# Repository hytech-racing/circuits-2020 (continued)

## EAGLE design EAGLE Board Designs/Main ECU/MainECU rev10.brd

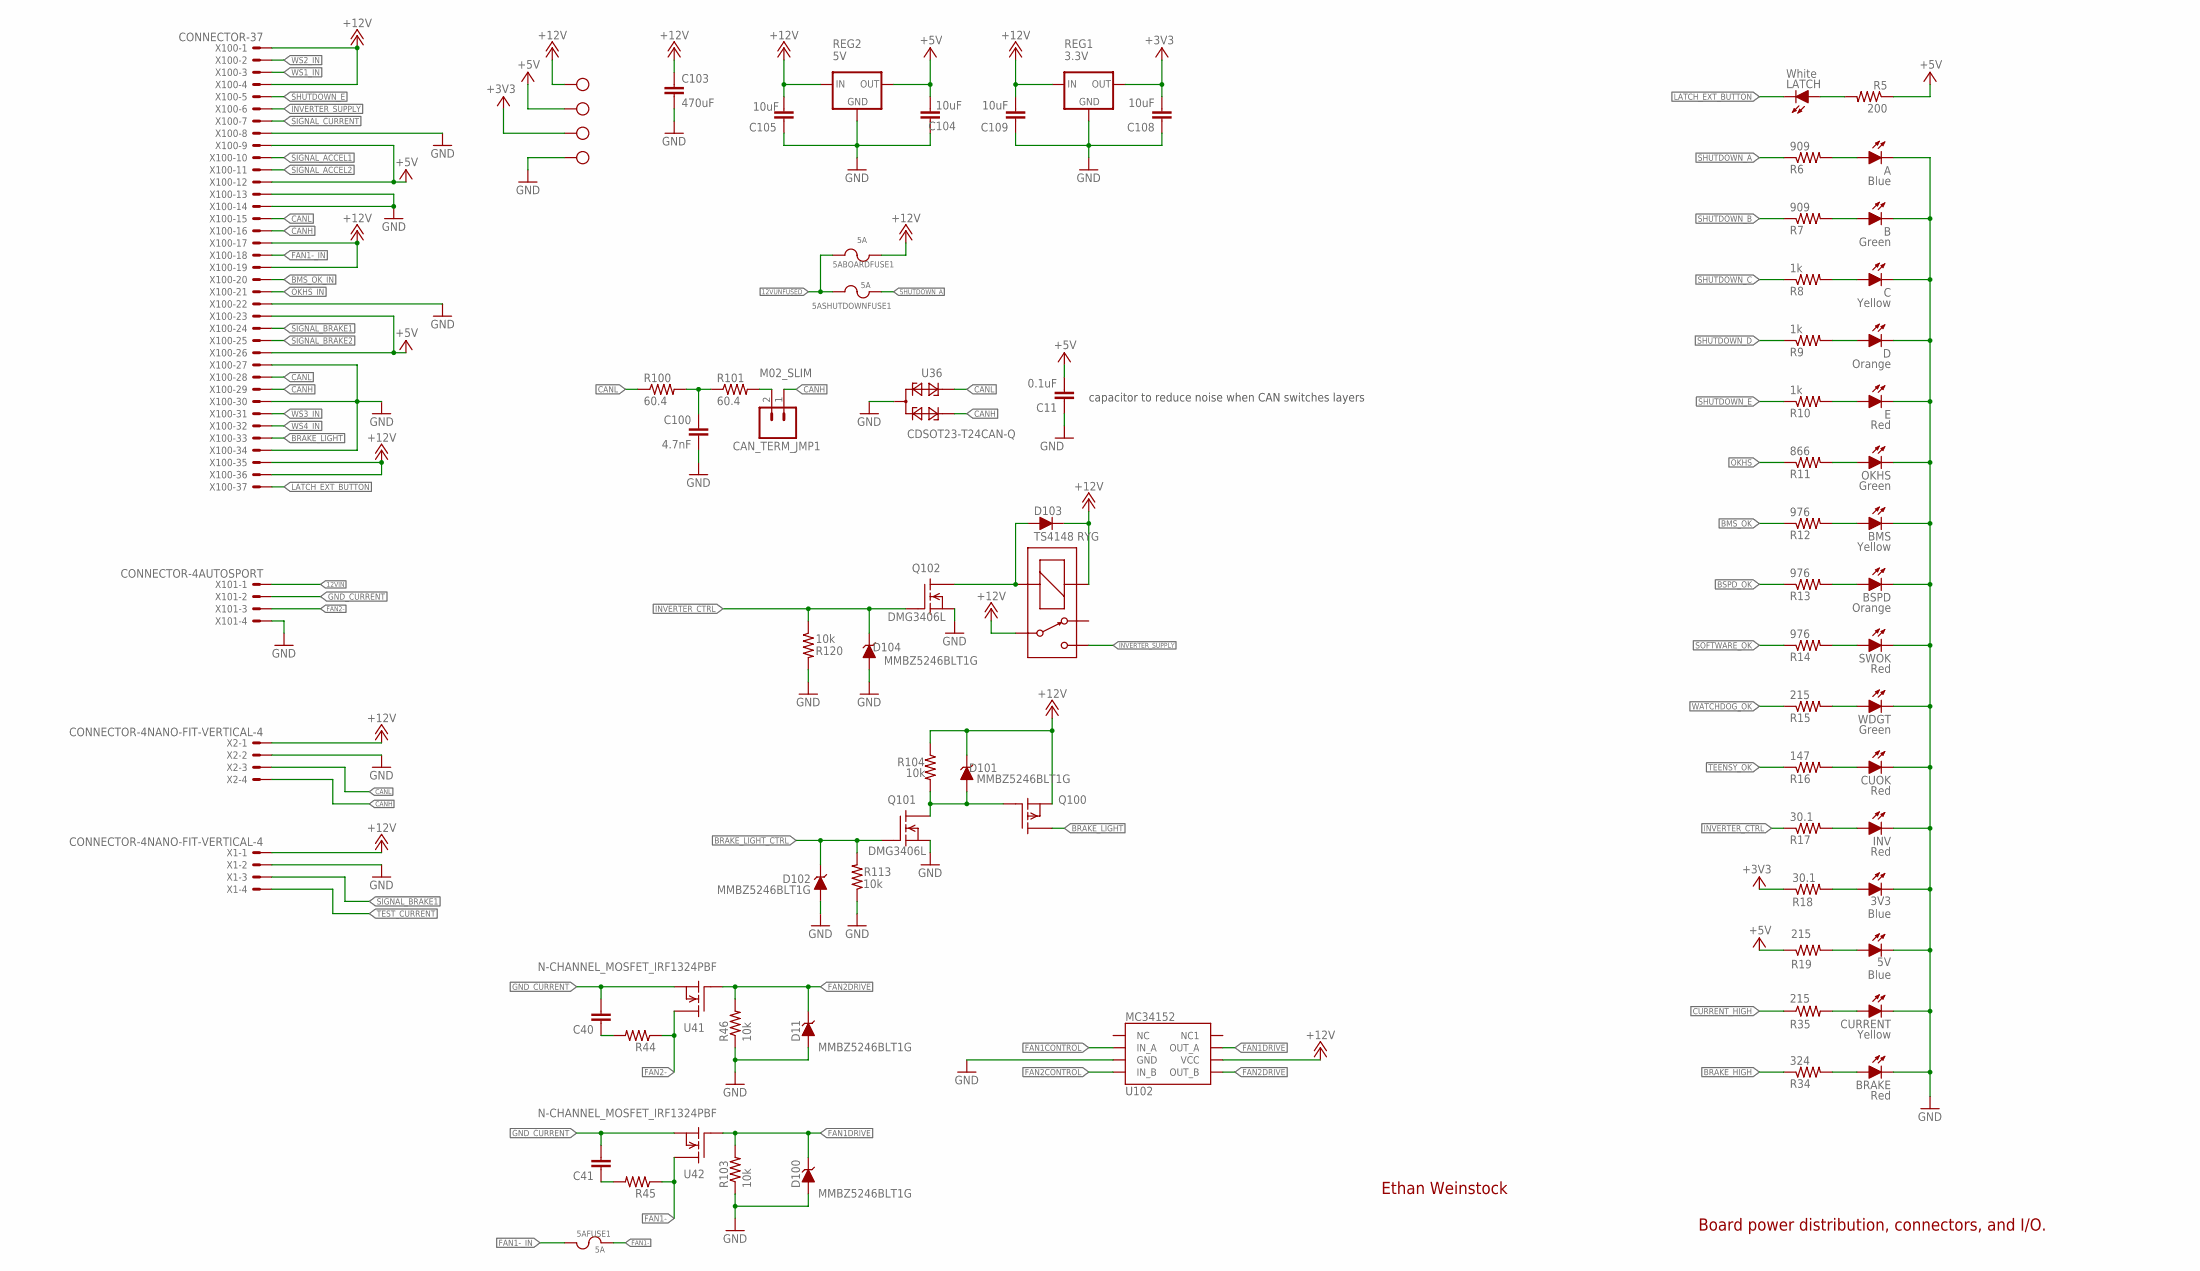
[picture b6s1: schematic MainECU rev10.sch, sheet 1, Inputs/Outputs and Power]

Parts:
3V3, 5V: Blue; LED-805
3V3_TEST: TEST_POINTMICRO_MINIATURE; MICRO_MINIATURE
5ABOARDFUSE1, 5AFUSE1, 5ASHUTDOWNFUSE1: 5A; MINI-BLADE_FUSE_HOLDER
12V_TEST: 12V_TEST; MICRO_MINIATURE
A: Blue; LED-805
B: Green; LED-805
BMS: Yellow; LED-805
BRAKE: Red; LED-805
BSPD: Orange; LED-805
C: Yellow; LED-805
C11: 0.1uF; 0603-CAP
C40, C41: CAP0603-CAP; 0603-CAP
C100: 4.7nF; 0603-CAP
C103: 470uF; CAP-PTH-LARGE
C104, C105, C108, C109: 10uF; 0603-CAP
CAN_TERM_JMP1: M02_SLIM; 1X02_SLIM
CUOK: Red; LED-805
CURRENT: Yellow; LED-805
D: Orange; LED-805
D11, D100, D101, D102, D104: MMBZ5246BLT1G; SOT23
D103: TS4148 RYG; 0805_D
E: Red; LED-805
INV: Red; LED-805
INVERTER_PWR_RELAY1: G5LE; ZF112
LATCH: White; LED-805
OKHS: Green; LED-805
Q100: P-CHANNEL_MOSFET_DMP3099L-7; SOT23
Q101, Q102: DMG3406L; SOT23
R5: 200; 0603-RES
R6, R7: 909; 0603-RES
R8, R9, R10: 1k; 0603-RES
R11: 866; 0603-RES
R12, R13, R14: 976; 0603-RES
R15, R19, R35: 215; 0603-RES
R16: 147; 0603-RES
R17, R18: 30.1; 0603-RES
R34: 324; 0603-RES
R44, R45: RESISTOR0603; 0603-RES
R46, R103, R104, R113, R120: 10k; 0603-RES
R100, R101: 60.4; 0603-RES
REG1: 3.3V; OKI-78SR
REG2: 5V; OKI-78SR
SWOK: Red; LED-805
U36: CDSOT23-T24CAN-Q; SOT23
U40, U43: TEST_POINTMICRO_MINIATURE; MICRO_MINIATURE
U41, U42: N-CHANNEL_MOSFET_IRF1324PBF; TO-220-H-HOLE
U102: MC34152; SOIC-08
WDGT: Green; LED-805
X1, X2: CONNECTOR-4NANO-FIT-VERTICAL-4; NANO-FIT_VERTICAL-4
X100: CONNECTOR-37; AUTOSPORT_14-35
X101: CONNECTOR-4AUTOSPORT; AUTOSPORT_12-04

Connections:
12VIN: X101.P$1; also elsewhere on the board
12VUNFUSED: 5ABOARDFUSE1.L1 (1), 5ABOARDFUSE1.L2 (1), 5ASHUTDOWNFUSE1.L1 (1), 5ASHUTDOWNFUSE1.L2 (1); also elsewhere on the board
+3V3: 3V3_TEST.P$1, C108.2, R18.1, REG1.3 (OUT); also elsewhere on the board
+5V: C11.2, C104.2, R5.1, R19.1, REG2.3 (OUT), U43.P$1, X100.P$9, X100.P$12, X100.P$23, X100.P$26; also elsewhere on the board
+12V: 5ABOARDFUSE1.R1 (2), 5ABOARDFUSE1.R2 (2), 12V_TEST.P$1, C103.1, C105.2, C109.2, D101.3 (C), D103.C, INVERTER_PWR_RELAY1.1 (COIL+), INVERTER_PWR_RELAY1.P, Q100.2 (S), R104.1, REG1.1 (IN), REG2.1 (IN), U102.6 (VCC), X1.P$1, X2.P$1, X100.P$1, X100.P$4, X100.P$17, X100.P$19, X100.P$35, X100.P$36; also elsewhere on the board
BMS_OK: R12.1; also elsewhere on the board
BMS_OK_IN: X100.P$20; also elsewhere on the board
BRAKE_HIGH: R34.1; also elsewhere on the board
BRAKE_LIGHT: Q100.3 (D), X100.P$33
BRAKE_LIGHT_CTRL: D102.3 (C), Q101.1 (G), R113.2; also elsewhere on the board
BSPD_OK: R13.1; also elsewhere on the board
CANH: CAN_TERM_JMP1.1, U36.2, X2.P$4, X100.P$16, X100.P$29; also elsewhere on the board
CANL: R100.1, U36.1, X2.P$3, X100.P$15, X100.P$28; also elsewhere on the board
CURRENT_HIGH: R35.1; also elsewhere on the board
FAN1-: 5AFUSE1.R1 (2), 5AFUSE1.R2 (2), R45.1, U42.2 (D)
FAN1-_IN: 5AFUSE1.L1 (1), 5AFUSE1.L2 (1), X100.P$18
FAN1CONTROL: U102.2 (IN_A); also elsewhere on the board
FAN1DRIVE: D100.3 (C), R103.2, U42.1 (G), U102.7 (OUT_A)
FAN2-: R44.1, U41.2 (D), X101.P$3
FAN2CONTROL: U102.4 (IN_B); also elsewhere on the board
FAN2DRIVE: D11.3 (C), R46.2, U41.1 (G), U102.5 (OUT_B)
GND: 3V3.C, 5V.C, A.C, B.C, BMS.C, BRAKE.C, BSPD.C, C.C, C11.1, C100.2, C103.2, C104.1, C105.1, C108.1, C109.1, CUOK.C, CURRENT.C, D.C, D11.1 (A), D100.1 (A), D102.1 (A), D104.1 (A), E.C, INV.C, OKHS.C, Q101.2 (S), Q102.2 (S), R46.1, R103.1, R113.1, R120.2, REG1.2 (GND), REG2.2 (GND), SWOK.C, U36.3, U40.P$1, U102.3 (GND), WDGT.C, X1.P$2, X2.P$2, X100.P$8, X100.P$13, X100.P$14, X100.P$22, X100.P$27, X100.P$30, X100.P$34, X101.P$4; also elsewhere on the board
GND_CURRENT: C40.2, C41.2, U41.3 (S), U42.3 (S), X101.P$2; also elsewhere on the board
INVERTER_CTRL: D104.3 (C), Q102.1 (G), R17.1, R120.1; also elsewhere on the board
INVERTER_SUPPLY: INVERTER_PWR_RELAY1.S, X100.P$6
LATCH_EXT_BUTTON: LATCH.C, X100.P$37; also elsewhere on the board
unnamed: E.A, R10.2
unnamed: R14.2, SWOK.A
unnamed: R15.2, WDGT.A
unnamed: CUOK.A, R16.2
unnamed: A.A, R6.2
unnamed: 3V3.A, R18.2
unnamed: C40.1, R44.2
unnamed: C41.1, R45.2
unnamed: B.A, R7.2
unnamed: C.A, R8.2
unnamed: LATCH.A, R5.2
unnamed: OKHS.A, R11.2
unnamed: BMS.A, R12.2
unnamed: CURRENT.A, R35.2
unnamed: BRAKE.A, R34.2
unnamed: BSPD.A, R13.2
unnamed: 5V.A, R19.2
unnamed: D101.1 (A), Q100.1 (G), Q101.3 (D), R104.2
unnamed: D.A, R9.2
unnamed: INV.A, R17.2
unnamed: D103.A, INVERTER_PWR_RELAY1.2 (COIL-), Q102.3 (D)
unnamed: CAN_TERM_JMP1.2, R101.2
unnamed: C100.1, R100.2, R101.1
OKHS: R11.1; also elsewhere on the board
OKHS_IN: X100.P$21; also elsewhere on the board
SHUTDOWN_A: 5ASHUTDOWNFUSE1.R1 (2), 5ASHUTDOWNFUSE1.R2 (2), R6.1; also elsewhere on the board
SHUTDOWN_B: R7.1; also elsewhere on the board
SHUTDOWN_C: R8.1; also elsewhere on the board
SHUTDOWN_D: R9.1; also elsewhere on the board
SHUTDOWN_E: R10.1, X100.P$5; also elsewhere on the board
SIGNAL_ACCEL1: X100.P$10; also elsewhere on the board
SIGNAL_ACCEL2: X100.P$11; also elsewhere on the board
SIGNAL_BRAKE1: X1.P$3, X100.P$24; also elsewhere on the board
SIGNAL_BRAKE2: X100.P$25; also elsewhere on the board
SIGNAL_CURRENT: X100.P$7; also elsewhere on the board
SOFTWARE_OK: R14.1; also elsewhere on the board
TEENSY_OK: R16.1; also elsewhere on the board
TEST_CURRENT: X1.P$4; also elsewhere on the board
WATCHDOG_OK: R15.1; also elsewhere on the board
WS1_IN: X100.P$3; also elsewhere on the board
WS2_IN: X100.P$2; also elsewhere on the board
WS3_IN: X100.P$31; also elsewhere on the board
WS4_IN: X100.P$32; also elsewhere on the board

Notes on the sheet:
Ethan Weinstock
Board power distribution, connectors, and I/O.
capacitor to reduce noise when CAN switches layers

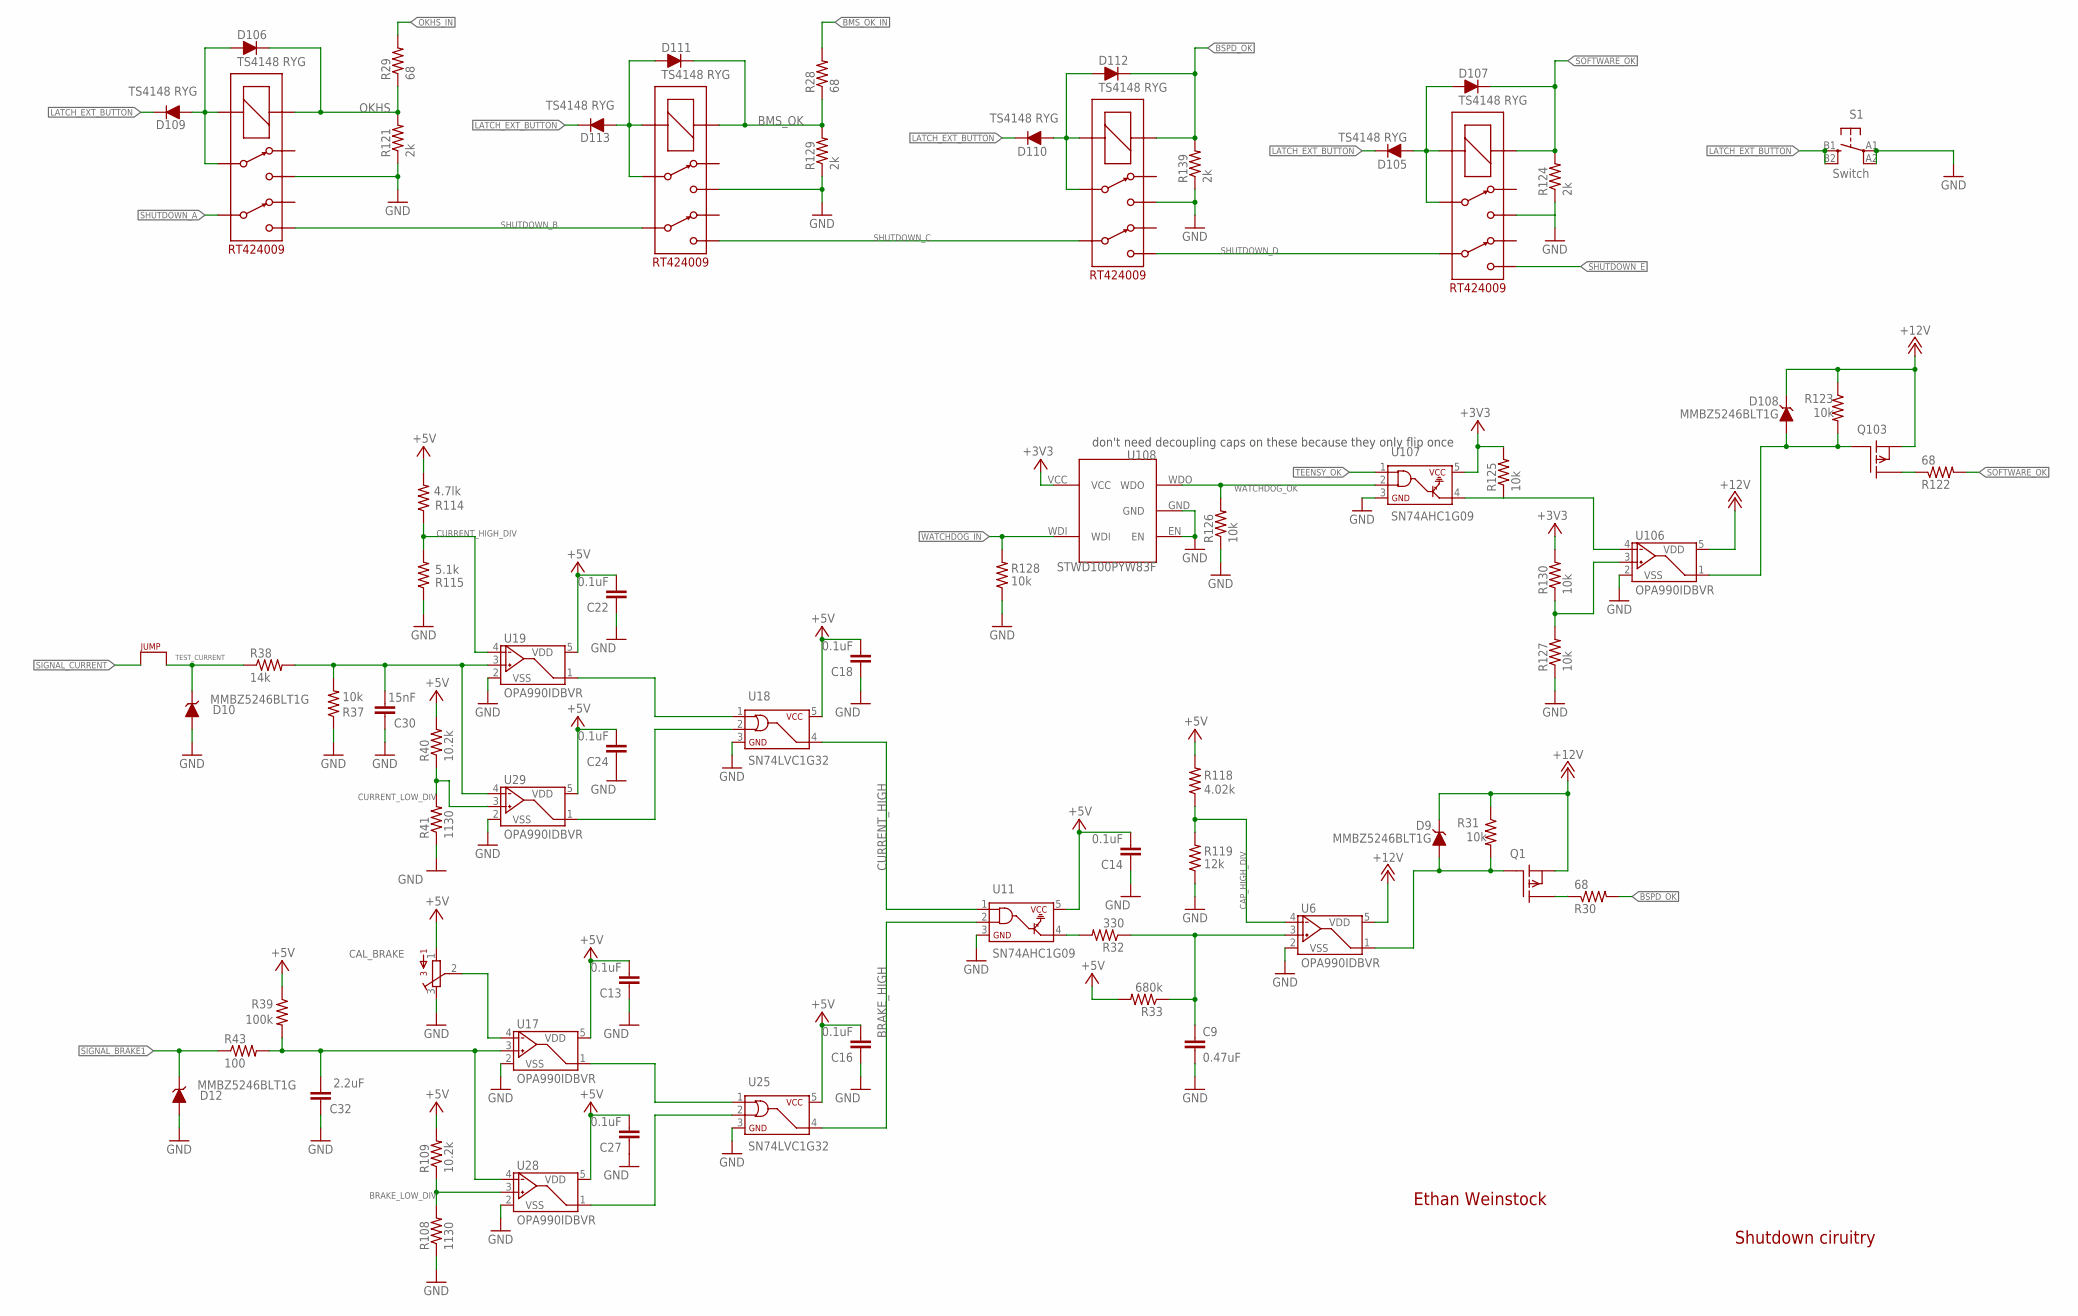
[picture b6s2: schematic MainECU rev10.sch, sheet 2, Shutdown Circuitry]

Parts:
C9: 0.47uF; 0603-CAP
C13, C14, C16, C18, C22, C24, C27: 0.1uF; 0603-CAP
C30: 15nF; 0603-CAP
C32: 2.2uF; 0603-CAP
CAL_BRAKE: TRIMPOT_3296C; TRIMPOT_3296
D9, D10, D12, D108: MMBZ5246BLT1G; SOT23
D105, D106, D107, D109, D110, D111, D112, D113: TS4148 RYG; 0805_D
IMD_SHUTDOWN_RLY1: RT424009; RELAY_DPDT
J1: JUMPER.1; 1X02
Q1, Q103: P-CHANNEL_MOSFET_DMP3099L-7; SOT23
R28, R29, R30, R122: 68; 0603-RES
R31, R37, R123, R125, R126, R127, R128, R130: 10k; 0603-RES
R32: 330; 0603-RES
R33: 680k; 0603-RES
R38: 14k; 0603-RES
R39: 100k; 0603-RES
R40, R109: 10.2k; 0603-RES
R41, R108: 1130; 0603-RES
R43: 100; 0603-RES
R114: 4.7lk; 0603-RES
R115: 5.1k; 0603-RES
R118: 4.02k; 0603-RES
R119: 12k; 0603-RES
R121, R124, R129, R139: 2k; 0603-RES
S1: Switch; TACTILE_SWITCH_SMD_6.2MM_TALL
U2, U3, U4: RT424009; RELAY_DPDT
U6, U17, U19, U28, U29, U106: OPA990IDBVR; SOT-23-5
U11, U107: SN74AHC1G09; SOT-23-5
U18, U25: SN74LVC1G32; SOT-23-5
U108: STWD100PYW83F; SOT323-5

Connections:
+3V3: R125.2, R130.2, U107.5, U108.VCC; also elsewhere on the board
+5V: C13.2, C14.2, C16.2, C18.2, C22.2, C24.2, C27.2, CAL_BRAKE.1, R33.2, R39.1, R40.2, R109.2, R114.2, R118.2, U11.5, U17.5 (VDD), U18.5 (VCC), U19.5 (VDD), U25.5 (VCC), U28.5 (VDD), U29.5 (VDD); also elsewhere on the board
+12V: D9.3 (C), D108.3 (C), Q1.2 (S), Q103.2 (S), R31.1, R123.1, U6.5 (VDD), U106.5 (VDD); also elsewhere on the board
BMS_OK: D111.C, R28.1, R129.2, U3.COIL+; also elsewhere on the board
BMS_OK_IN: R28.2; also elsewhere on the board
BMS_PWR_STEP1: D111.A, D113.A, U3.3, U3.COIL-
BRAKE_HIGH: U11.2, U25.4 (Y); also elsewhere on the board
BRAKE_LOW_DIV: R108.2, R109.1, U28.3 (VIN+)
BSPD_OK: D112.C, R30.2, R139.2, U2.COIL+; also elsewhere on the board
CAP_HIGH_DIV: R118.1, R119.2, U6.4 (VIN-)
CURRENT_HIGH: U11.1, U18.4 (Y); also elsewhere on the board
CURRENT_HIGH_DIV: R114.1, R115.2, U19.4 (VIN-)
CURRENT_LOW_DIV: R40.1, R41.2, U29.3 (VIN+)
GND: C9.2, C13.1, C14.1, C16.1, C18.1, C22.1, C24.1, C27.1, C30.1, C32.1, CAL_BRAKE.3, D10.1 (A), D12.1 (A), IMD_SHUTDOWN_RLY1.4, R37.1, R41.1, R108.1, R115.1, R119.1, R121.1, R124.1, R126.1, R127.1, R128.1, R129.1, R139.1, S1.A1, S1.A2 (P1), U2.4, U3.4, U4.4, U6.2 (VSS), U11.3, U17.2 (VSS), U18.3 (GND), U19.2 (VSS), U25.3 (GND), U28.2 (VSS), U29.2 (VSS), U106.2 (VSS), U107.3, U108.EN, U108.GND; also elsewhere on the board
IMD_PWR_STEP1: D106.A, D109.A, IMD_SHUTDOWN_RLY1.3, IMD_SHUTDOWN_RLY1.COIL-
LATCH_EXT_BUTTON: D105.C, D109.C, D110.C, D113.C, S1.B1 (S), S1.B2 (S1); also elsewhere on the board
unnamed: Q1.3 (D), R30.1
unnamed: C32.2, R39.2, R43.2, U17.3 (VIN+), U28.4 (VIN-)
unnamed: U17.1 (VOUT), U25.1 (A)
unnamed: D105.A, D107.A, U4.3, U4.COIL-
unnamed: U25.2 (B), U28.1 (VOUT)
unnamed: D108.1 (A), Q103.1 (G), R123.2, U106.1 (VOUT)
unnamed: Q103.3 (D), R122.1
unnamed: CAL_BRAKE.2, U17.4 (VIN-)
unnamed: U18.1 (A), U19.1 (VOUT)
unnamed: U18.2 (B), U29.1 (VOUT)
unnamed: R125.1, U106.4 (VIN-), U107.4
unnamed: R127.2, R130.1, U106.3 (VIN+)
unnamed: D110.A, D112.A, U2.3, U2.COIL-
unnamed: C30.2, R37.2, R38.2, U19.3 (VIN+), U29.4 (VIN-)
unnamed: R32.2, U11.4
unnamed: C9.1, R32.1, R33.1, U6.3 (VIN+)
unnamed: D9.1 (A), Q1.1 (G), R31.2, U6.1 (VOUT)
OKHS: D106.C, IMD_SHUTDOWN_RLY1.COIL+, R29.1, R121.2; also elsewhere on the board
OKHS_IN: R29.2; also elsewhere on the board
SHUTDOWN_A: IMD_SHUTDOWN_RLY1.6; also elsewhere on the board
SHUTDOWN_B: IMD_SHUTDOWN_RLY1.5, U3.6; also elsewhere on the board
SHUTDOWN_C: U2.6, U3.5; also elsewhere on the board
SHUTDOWN_D: U2.5, U4.6; also elsewhere on the board
SHUTDOWN_E: U4.5; also elsewhere on the board
SIGNAL_BRAKE1: D12.3 (C), R43.1; also elsewhere on the board
SIGNAL_CURRENT: J1.1; also elsewhere on the board
SOFTWARE_OK: D107.C, R122.2, R124.2, U4.COIL+; also elsewhere on the board
TEENSY_OK: U107.1; also elsewhere on the board
TEST_CURRENT: D10.3 (C), J1.2, R38.1; also elsewhere on the board
WATCHDOG_IN: R128.2, U108.WDI; also elsewhere on the board
WATCHDOG_OK: R126.2, U107.2, U108.WDO; also elsewhere on the board

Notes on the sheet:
Ethan Weinstock
Shutdown ciruitry
don't need decoupling caps on these because they only flip once

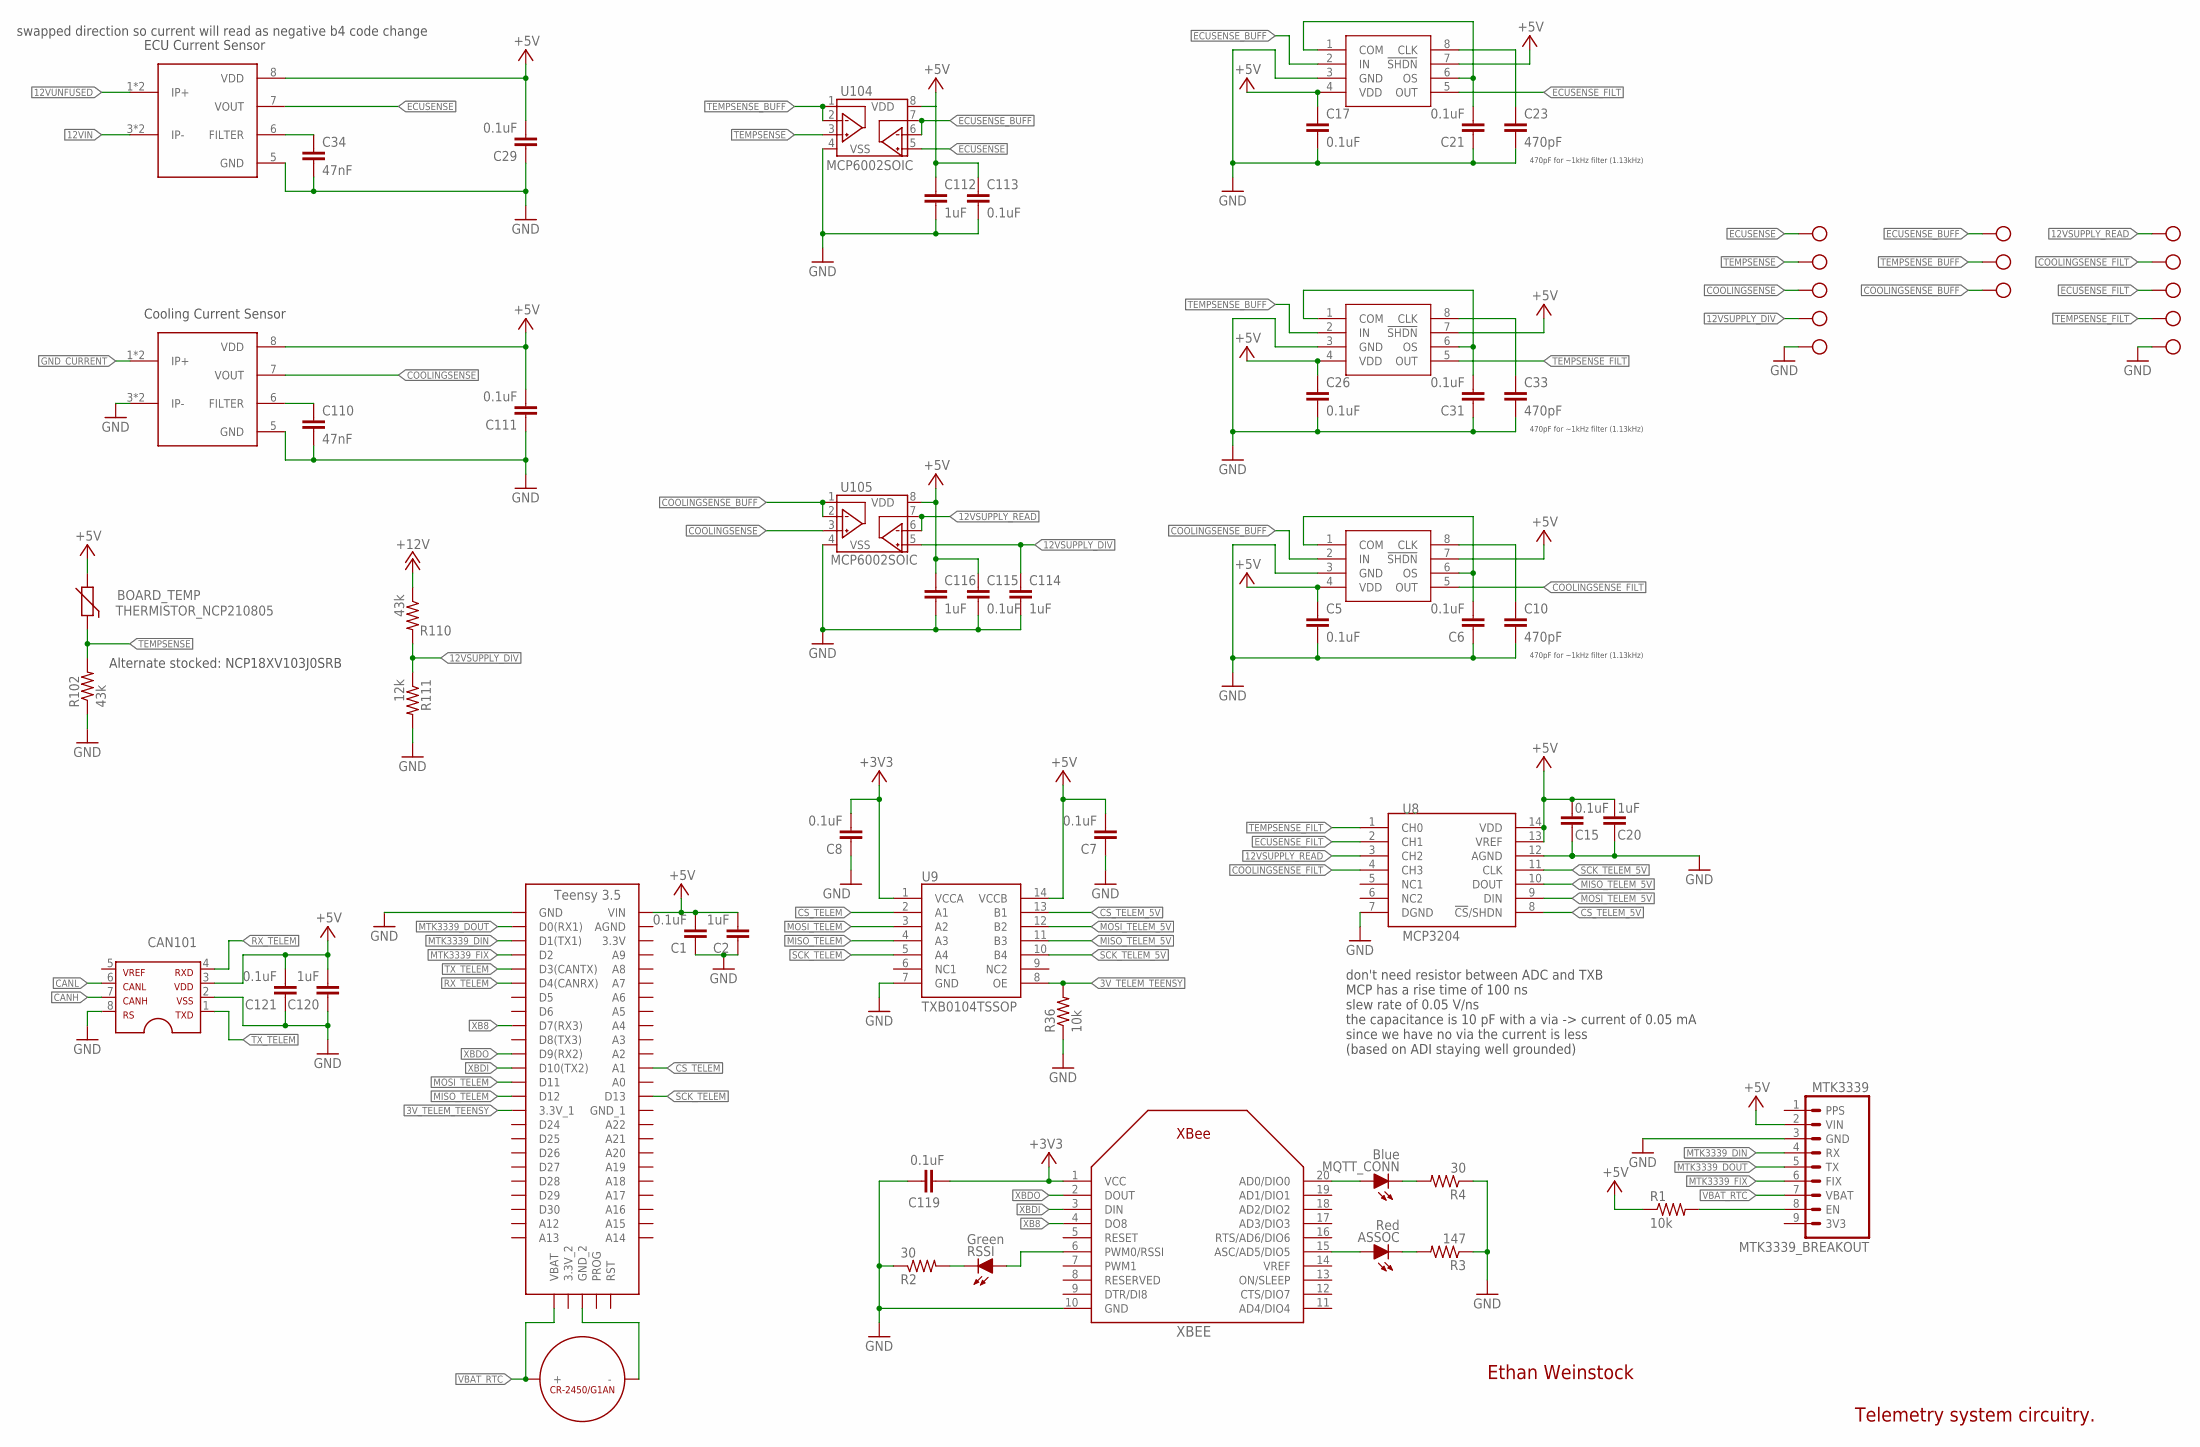
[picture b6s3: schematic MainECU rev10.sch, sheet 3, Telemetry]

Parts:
ASSOC: Red; LED-805
BOARD_TEMP: THERMISTOR_NCP210805; 0805
C1, C5, C6, C7, C8, C15, C17, C21, C26, C29, C31, C111, C113, C115, C119, C121: 0.1uF; 0603-CAP
C2, C20, C112, C114, C116, C120: 1uF; 0603-CAP
C10, C23, C33: 470pF; 0603-CAP
C34, C110: 47nF; 0603-CAP
CAN101: MCP2551; SOIC-08
MQTT_CONN: Blue; LED-805
MTK3339_BREAKOUT: MTK3339; 1X09
R1, R36: 10k; 0603-RES
R2, R4: 30; 0603-RES
R3: 147; 0603-RES
R102, R110: 43k; 0603-RES
R111: 12k; 0603-RES
RSSI: Green; LED-805
U1: TEENSY_3.5_EXT
U7, U24, U33: MAX7480; SOIC-08
U8: MCP3204; SO14
U9: TXB0104TSSOP; TSSOP-14
U12, U13, U14, U15, U16, U20, U21, U22, U26, U27, U30, U31, U32: TEST_POINTMICRO_MINIATURE; MICRO_MINIATURE
U35, U103: ACHS-7121; SOP8
U104, U105: MCP6002SOIC; SOIC-08
U109: CR-2450/G1AN
XBEE: XBEE

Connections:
3V_TELEM_TEENSY: R36.2, U1.3.3V_1, U9.8 (OE)
12VIN: U35.3 (IP-), U35.4 (IP-); also elsewhere on the board
12VSUPPLY_DIV: C114.1, R110.2, R111.1, U16.P$1, U105.5 (VINB+)
12VSUPPLY_READ: U8.3 (CH2), U15.P$1, U105.6 (VINB-), U105.7 (VOUTB)
12VUNFUSED: U35.1 (IP+), U35.2 (IP+); also elsewhere on the board
+3V3: C8.2, C119.1, U9.1 (VCCA), XBEE.1 (VCC); also elsewhere on the board
+5V: BOARD_TEMP.1, C1.2, C2.2, C5.1, C7.2, C15.2, C17.1, C20.2, C26.1, C29.2, C111.2, C112.1, C113.1, C115.1, C116.1, C120.2, C121.2, CAN101.3, MTK3339_BREAKOUT.2 (VIN), R1.1, U1.VIN, U7.4 (VDD), U7.7 (!SHDN), U8.13 (VREF), U8.14 (VDD), U9.14 (VCCB), U24.4 (VDD), U24.7 (!SHDN), U33.4 (VDD), U33.7 (!SHDN), U35.8 (VDD), U103.8 (VDD), U104.8 (VDD), U105.8 (VDD); also elsewhere on the board
+12V: R110.1; also elsewhere on the board
CANH: CAN101.7; also elsewhere on the board
CANL: CAN101.6; also elsewhere on the board
COOLINGSENSE: U21.P$1, U103.7 (VOUT), U105.3 (VINA+)
COOLINGSENSE_BUFF: U7.2 (IN), U12.P$1, U105.1 (VOUTA), U105.2 (VINA-)
COOLINGSENSE_FILT: U7.5 (OUT), U8.4 (CH3), U20.P$1
CS_TELEM: U1.A1, U9.2 (A1)
CS_TELEM_5V: U8.8 (!CS!/SHDN), U9.13 (B1)
ECUSENSE: U27.P$1, U35.7 (VOUT), U104.5 (VINB+)
ECUSENSE_BUFF: U13.P$1, U24.2 (IN), U104.6 (VINB-), U104.7 (VOUTB)
ECUSENSE_FILT: U8.2 (CH1), U24.5 (OUT), U26.P$1
GND: C1.1, C2.1, C5.2, C6.1, C7.1, C8.1, C10.2, C15.1, C17.2, C20.1, C21.1, C23.2, C26.2, C29.1, C31.1, C33.2, C34.2, C110.2, C111.1, C112.2, C113.2, C114.2, C115.2, C116.2, C119.2, C120.1, C121.1, CAN101.2, CAN101.8, MTK3339_BREAKOUT.3 (GND), R2.1, R3.1, R4.1, R36.1, R102.1, R111.2, U1.GND, U7.3 (GND), U8.7 (DGND), U8.12 (AGND), U9.7 (GND), U22.P$1, U24.3 (GND), U32.P$1, U33.3 (GND), U35.5 (GND), U103.3 (IP-), U103.4 (IP-), U103.5 (GND), U104.4 (VSS), U105.4 (VSS), XBEE.10 (GND); also elsewhere on the board
GND_CURRENT: U103.1 (IP+), U103.2 (IP+); also elsewhere on the board
MISO_TELEM: U1.D12, U9.4 (A3)
MISO_TELEM_5V: U8.10 (DOUT), U9.11 (B3)
MOSI_TELEM: U1.D11, U9.3 (A2)
MOSI_TELEM_5V: U8.9 (DIN), U9.12 (B2)
MTK3339_DIN: MTK3339_BREAKOUT.4 (RX), U1.D1(TX1)
MTK3339_DOUT: MTK3339_BREAKOUT.5 (TX), U1.D0(RX1)
MTK3339_FIX: MTK3339_BREAKOUT.6 (FIX), U1.D2
unnamed: C10.1, U7.8 (CLK)
unnamed: C6.2, U7.1 (COM), U7.6 (OS)
unnamed: C110.1, U103.6 (FILTER)
unnamed: C34.1, U35.6 (FILTER)
unnamed: R2.2, RSSI.C
unnamed: RSSI.A, XBEE.6 (PWM0/RSSI)
unnamed: ASSOC.A, XBEE.15 (ASC/AD5/DIO5)
unnamed: ASSOC.C, R3.2
unnamed: MQTT_CONN.C, R4.2
unnamed: MQTT_CONN.A, XBEE.20 (AD0/DIO0)
unnamed: U1.GND_2, U109.-
unnamed: C33.1, U33.8 (CLK)
unnamed: C23.1, U24.8 (CLK)
unnamed: MTK3339_BREAKOUT.8 (EN), R1.2
unnamed: C21.2, U24.1 (COM), U24.6 (OS)
unnamed: C31.2, U33.1 (COM), U33.6 (OS)
RX_TELEM: CAN101.4, U1.D4(CANRX)
SCK_TELEM: U1.D13, U9.5 (A4)
SCK_TELEM_5V: U8.11 (CLK), U9.10 (B4)
TEMPSENSE: BOARD_TEMP.2, R102.2, U31.P$1, U104.3 (VINA+)
TEMPSENSE_BUFF: U14.P$1, U33.2 (IN), U104.1 (VOUTA), U104.2 (VINA-)
TEMPSENSE_FILT: U8.1 (CH0), U30.P$1, U33.5 (OUT)
TX_TELEM: CAN101.1, U1.D3(CANTX)
VBAT_RTC: MTK3339_BREAKOUT.7 (VBAT), U1.VBAT, U109.+_0 (+), U109.+_1 (+)
XB8: U1.D7(RX3), XBEE.4 (DO8)
XBDI: U1.D10(TX2), XBEE.3 (DIN)
XBDO: U1.D9(RX2), XBEE.2 (DOUT)

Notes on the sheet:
ECU Current Sensor
Cooling Current Sensor
470pF for ~1kHz filter (1.13kHz)
Alternate stocked: NCP18XV103J0SRB
Ethan Weinstock
Telemetry system circuitry.
don't need resistor between ADC and TXB MCP has a rise time of 100 ns slew rate of 0.05 V/ns the capacitance is 10 pF with a via -> current of 0.05 mA since we have no via the current is less (based on ADI staying well grounded)
swapped direction so current will read as negative b4 code change

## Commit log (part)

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2020-11-09 Changed 555 Capacitors
2020-11-09 555 decoupler from 0.01 to 1 uF
2020-11-10 i rigged it
2020-11-11 More BSPD work
2020-11-11 Made schematic cleaner.
2020-11-11 Some design config
2020-11-12 Reflecting master version of HV board rev12
2020-11-12 More work on HV board rev13
2020-11-12 Schematic cleanup
2020-11-12 Adjusted minorly
2020-11-12 Fixed minor overlap
2020-11-12 Attempt to fix too large text on sheets
2020-11-12 Adjusted slighty
2020-11-13 Ecu rev10 analog split (#62)
    * Start working rev 10
    * Started schematic changes
    Removed dashboard components
    Changed shutdown circuit to OPA990
    * Updated shutdown circuitry
    Added OR gates
2020-11-14 Changed 0.76 gain to 0.75
2020-11-14 Updated BSPD design with new signal_current section
2020-11-15 Trying to get target resistance
2020-11-15 Ready to design
2020-11-17 Improvements to make debugging easier
2020-11-18 Added 3.3Volt power to ADIS chip
2020-11-18 Added placement via
2020-11-20 I just added a cap sorry
2020-11-20 Added labels for pads
2020-11-20 Made more compact, adjusted labels
2020-11-21 Made more changes to implement the e-fuse into the board including adding a current monitoring signal.
2020-11-22 Fixed erc warnings on rev12 (#64)
2020-11-22 Revert "Made schematic cleaner."
    This reverts commit db1da438f102cfb554297d19687bd75e05db3550.
2020-11-24 Altered the traces of the board, added two IMON resistors, changed the Shutdown signals to be analog inputs rather than digital on the teensy
2020-11-25 Changed GND of LEDs, cleaned up routing
2020-11-25 CAN Traffic Teensy Boards
    Renamed all the CAN Traffic boards from "Transceiver" to "Traffic Teensy X.X"
2020-11-27 Altered the orientation of the e-fuse and made changes to the trace widths
2020-11-28 Added separate workspace for pcb tester
2020-11-28 Added to Dash
2020-11-29 Changed brakeside to pull-up
2020-11-29 HV section done
2020-11-29 progress
2020-11-29 Nearly done
2020-11-29 Almost done
2020-11-29 Routed R1 and R2 on brake side
2020-11-30 Added resistor diode pairs for signals being monitored and added a button to reset the efuses if tripped
2020-11-30 Made silk screen look better and made the schematic look better
2020-11-30 Adjusted HV area
2020-11-30 Further fixes
2020-12-01 Changes accidentally on hv branch
2020-12-01 Added wheel speed circuit
2020-12-01 Specified resistor vals for digipot
2020-12-01 added the new na555 timer schematic
2020-12-02 Added the gate resistor and made the text on the symbols layer
2020-12-02 What I went over in shop
2020-12-02 add pad for ground
2020-12-02 Changed a zener diode to a tvs diode and got rid of the LED silkscreen
2020-12-02 Final fixes
2020-12-02 Finished
2020-12-02 Probably done
2020-12-02 I'm 90% percent sure I'm doen
2020-12-04 Replaced e-fuse with old keystone fuse
2020-12-04 Updated board size and trace widths
2020-12-06 Updated design with some minor changes
2020-12-06 initial schematic
2020-12-06 create board and adjust schematic for different pin layout
2020-12-07 Silkscreen changes
2020-12-07 Added 5th sheet for HV
2020-12-07 Added 12V Control, TSAL+, SHUTDOWNE, IMDOK, Charge, BMS, and IMD
2020-12-07 dashboard buttons, main ecu 5v dac, 12v dac, 12v outputs, 12v inputs
2020-12-08 Revert "dashboard buttons, main ecu 5v dac, 12v dac, 12v outputs, 12v inputs"
    This reverts commit 0013d9e852ae6acf6c2814f2a50be84fd7b6edb7.
2020-12-08 Recreated pcb tester board file
2020-12-08 change signal reads on main ecu test board
2020-12-09 Changes in board review
    This reverts commit d30a44cf333b6e75a81830c5357fabca05badc4e.
2020-12-09 Made the changes described in the baord design meeting
2020-12-09 Made some changes talked about in the board review
2020-12-09 Revised analog input signals
2020-12-09 switch 12v ins and outs on main ecu
2020-12-09 change silkscreen
2020-12-11 Revert "Replaced jumpered resistors with digipot"
    This reverts commit 3ec4fa1ead4dac01abca876bc4bd114703f8871f.
2020-12-12 add initial basic circuit
2020-12-12 Changed resistor array values to usable values found in shop b/w 1k and 20k
2020-12-12 Switched Resistor associated with astable 555 timer to 43k from 100k
2020-12-12 Changed 555 timer capcitors to 1uF. See excel sheet
2020-12-14 Added frame to schematic
2020-12-15 Updated resistor values to actual rev1 board
2020-12-17 Made it so that there were no drc errors
2020-12-17 Made everything look a bit better
2020-12-20 incomplete changes to schamatic for rev3 features
2020-12-23 created dc dc converter schematic
2020-12-26 ECU rev11 wheelspeed circuit
2020-12-28 Updated names to wires
2020-12-29 TLV7021 based wheel-speed circuit
2020-12-30 Made some minor changes
2021-01-02 Created BSPD rev11 v3 in LTspice
2021-01-02 Fixed BSPD circuit
2021-01-03 Reformatting some files
2021-01-03 Added digipot wheel speed tester
2021-01-04 schematic
2021-01-06 finish board
2021-01-06 Create Sensor Acquisition Board Rev1.sch
    Added ATMEGA328P and CAN Interface/Controller
2021-01-06 Changed DRC
2021-01-06 moved chip name to bValues layer
2021-01-06 small changes for JLC DRC
2021-01-13 update schematic and board based on feedback
2021-01-15 Made changes
2021-01-17 Added new cap and made board
2021-01-17 changed plane sizes, fixed traces
2021-01-18 Made changes to the board layout to be the correct size
2021-01-19 Fnished schematic (completed the signal processing portion) and made board
2021-01-20 Minor deletions because of the sensor board
2021-01-20 So close to being done (updated board)
2021-01-21 Wired everything but 5V and GND
2021-01-22 add ratsnest
2021-01-22 small schematic edits
2021-01-24 Deleted old libraries
2021-01-26 Made PCB one sided
2021-01-27 fixed mistakes in ESF version of BSPD rev10
2021-01-31 Fixed the packages
2021-01-31 fixed git's fun with dc-dc
2021-02-01 Rename Power Switching Circuit.sch to Power Switching Circuit rev1.sch
2021-02-03 Finished TCAN337 breakout board
2021-02-03 Updated connectors on tcan board
2021-02-07 Trouble with routing traces to connect everything together
2021-02-07 Did part of the routing
2021-02-08 Shrunk board size slightly
2021-02-12 Finished dc dc board
2021-02-12 Updated dc dc converter
2021-02-18 fix drill size
2021-02-22 New bms work
    Didn't finish in one day. Screw modules
2021-02-23 Renamed PCB Tester files
2021-02-23 Added documentation copy into folder
    Easy access
2021-02-23 Added Notes
2021-02-23 Rearranged and added more Wheel speed testers
2021-02-23 Linked 555s to digipot and linked ground switch
2021-02-23 Finished BMS schematic
2021-02-24 Minor BMS update
2021-02-24 Removed GND switch
2021-02-24 Updated libraries and zener diode arrays
2021-02-26 trying eagle hack
2021-02-26 Design Review Changes
    Made the board much more compact and implemented schematic and board changes which were discussed during the 2/14 design review session
2021-02-26 Board size decrease
    Changed arrangement of autosport connections to make board even smaller
2021-02-26 Revert "Basic work"
    This reverts commit 314f29d0700f840b339ecbc3c92328a4e326f93a.
2021-02-27 started working on new system diagram
2021-02-27 more edits to dashboard
2021-02-28 updated main ecu io
2021-02-28 Minor BMS stuff
2021-03-01 small edits
2021-03-01 Adjusted name
2021-03-02 finishing up TS, shutdown, edits to power switching
2021-03-02 small aesthetic fixes
2021-03-02 power switching small edit
2021-03-02 added TSAL
2021-03-03 bms work
2021-03-05 exported image used in design event presentation
2021-03-08 started placing ltc6813
2021-03-09 Changed component layout and made more compact
2021-03-09 Ethan's updates
2021-03-09 Arranged board
2021-03-09 Revert "Updated components"
    This reverts commit 17738ee7e39cd48c0433d715aaeb9ad424bef63a.
2021-03-09 Revert "Updated components"
    This reverts commit b426657635f6be1200a4b060d109cd40c8cd37f9.
2021-03-09 Changed components
2021-03-09 Reorg schematic with new components
2021-03-09 First rev of board
2021-03-10 E fuse (#66)
    * Created the schematic and pcb layout for the TPS26600 testing board
    * Made changes to the pcb and schematic to comply with Hytech conventions
    * Changed the pcb and schematic layouts to comply with Hytech standards
    * Updated the E-Fuse board so that it is ready for production
    * Created a schematic for the TPS26630 breakout board and began the pcb layout
    * Finished the TPS26630 E-Fuse breakout board layout
2021-03-10 Started dashboard tester
2021-03-11 Updates routing and polygons
2021-03-11 Added teensy
2021-03-11 Fixed output connector
2021-03-12 Simplified switches, More cooling
    Replaced MAX4622 with ADG1423
    Moved logos and resistors on the right upwards
    Expanded thermal copper for LEDs
2021-03-12 Minor DRC fixes
2021-03-15 Control connections to teensy
2021-03-15 Rearranged control-teensy connections
2021-03-15 Routed control signals
2021-03-15 Rearranged pin config
2021-03-16 Fixed 3v3 connection
2021-03-18 Added mount holes and made minor polygon changes
2021-03-18 rev3 of battery discharge monitoring board
2021-03-19 Made final changes to DC DC Converter Board
2021-03-19 Added a silkscreen to the board
2021-03-19 Made final changes
2021-03-19 Cleaned up silkscreen
2021-03-20 More progress
2021-03-21 Schematic more readable
2021-03-21 Resolved issues with power switching connectors
2021-03-21 FIxed routing to remove clearance errors
2021-03-22 Fixed connection to control signals
2021-03-28 Changed the layer of the dimensions
2021-03-29 Created the new revision file.
2021-03-29 Added aesthetic and board test point changes
2021-03-30 make just adm823 board for testing
2021-04-03 Added some stuff and took some things away
2021-04-04 Added the new parts to the board with a change to the board design
2021-04-05 Minor fixes to resistor values
2021-04-06 Switched in MAX7400 filters and MCP2515 and remade board
2021-04-06 Hv board rev 13 (#71)
    * Work in progress
    * Adjusted library
    * Continued routing
    * Fixing eagle part
    * Adjusted filter positions
    * Fixed library part for isolated gate driver
2021-04-07 Rev2_1 schematic
2021-04-07 Made Board good (ie. finished board)
2021-04-07 fixed some issues
2021-04-08 made a little smaller
2021-04-08 Made some more board changes
2021-04-08 Final changes
2021-04-09 Cleaned up design and renumbered parts
2021-04-09 Hi Ethan
2021-04-09 Gerber should be good
2021-04-09 The board is good
2021-04-09 Revert "Revert "The board is good""
    This reverts commit b015c37795e48e196a3b81e850102cc3a7ea3226.
2021-04-09 Final changes to board design made.
2021-04-09 Should be done
2021-04-13 Dashboard rev3
2021-04-24 Update to be consistent with board
2021-05-10 Delete Power Switching Circuit rev1_2021-03-21.zip
    Unnecessary file
2021-05-10 Delete Power Switching Circuit rev1 - old.sch
    Unnecessary file
2021-05-10 rev2: different mosfets + added test points
2021-05-10 Updated 3 pin autosport and relay footprints
2021-05-11 Modified mosfet footprint
2021-05-15 Minor changes for sense resistor location
2021-05-16 Mosfet location changes
2021-05-17 Wrong file
2021-06-05 Added IC and external components
2021-06-05 Put rev3 changes in rev2 schem
2021-06-05 MCP 2551 -> MCP2562FD in Rev3 File
2021-06-06 Added rest of circuitry
    Added test points to connect wires to
    Added jumper so you can measure current output (I recommend)
2021-06-09 Created LTC3200-5 breakout board
2021-06-12 Finished all traces on board, still yet to pass DRC
2021-06-12 Started Tracing
2021-06-16 System diagram (#80)
    * started working on new system diagram
    * more edits to dashboard
    * updated main ecu io
    * updated system in front of firewall
    * small edits
    * TS internals updates
2021-06-16 Hv board rev 14 (#81)
    * Work in progress
    * Adjusted library
    * Continued routing
    * Fixing eagle part
    * Adjusted filter positions
    * Fixed library part for isolated gate driver
2021-06-16 TSAL rev3 (#79)
    * Created a copy of TSAL rev 2 to make minor changes
    * Changed the size of the pads, moved the resitor names to the right side of the board, and moved the traces so that the silk screen is visible
    * Finished making the revisions for rev 3 of the TSAL
    * Copied Rev2 schematic to connect to the rev3 board
    * Made the board and schematic consistent
    * Altered the silk screen so that it said rev 3 instead of rev 2
2021-06-18 New bspd resistor values
2021-06-24 Small update
2021-07-13 Changed MCerror to green
2021-07-13 Added LED
